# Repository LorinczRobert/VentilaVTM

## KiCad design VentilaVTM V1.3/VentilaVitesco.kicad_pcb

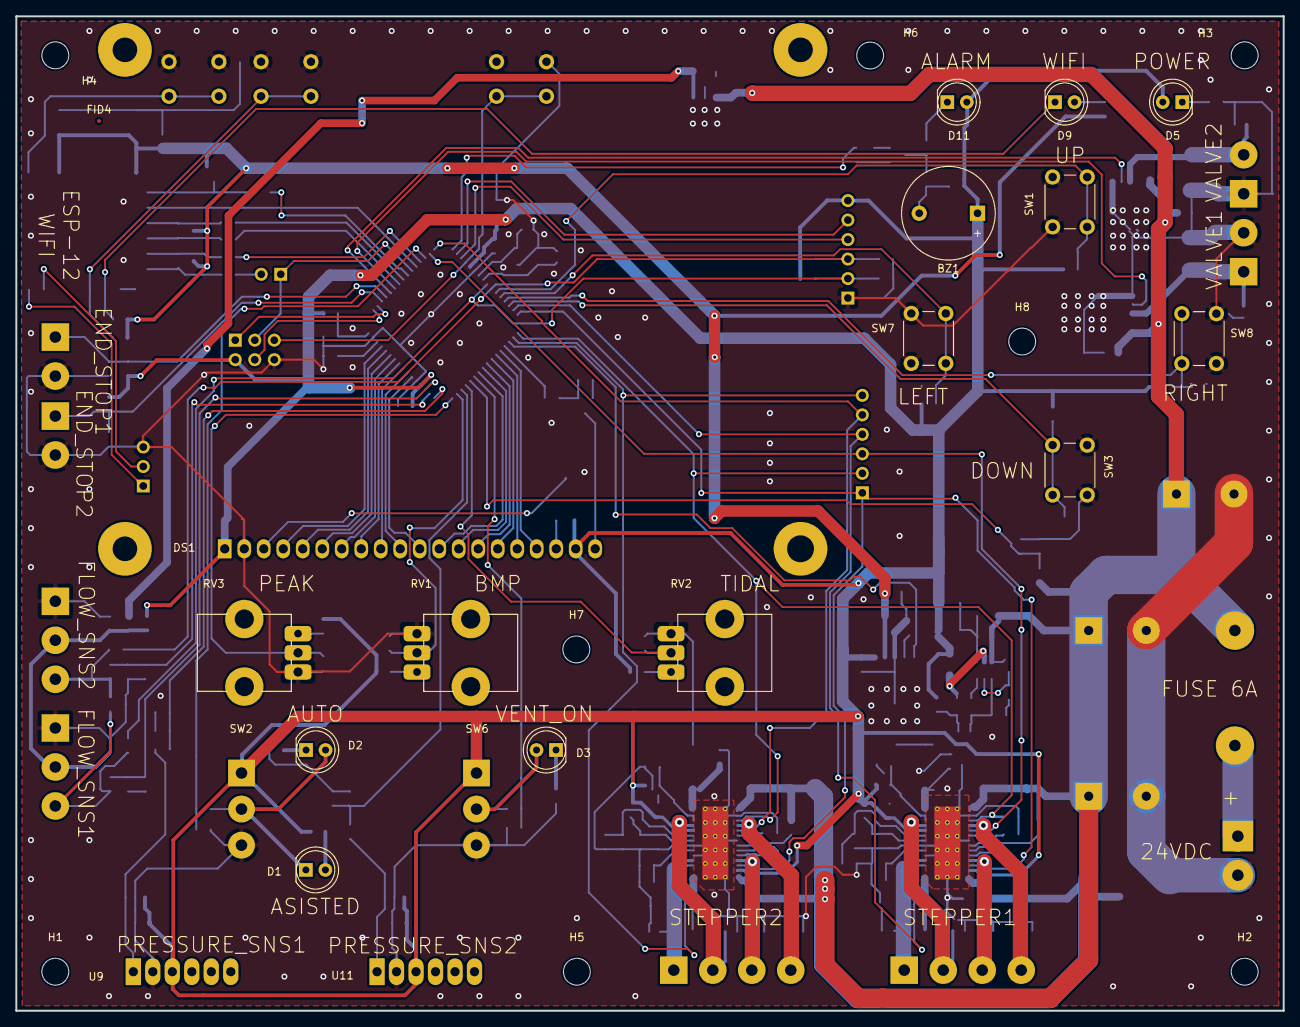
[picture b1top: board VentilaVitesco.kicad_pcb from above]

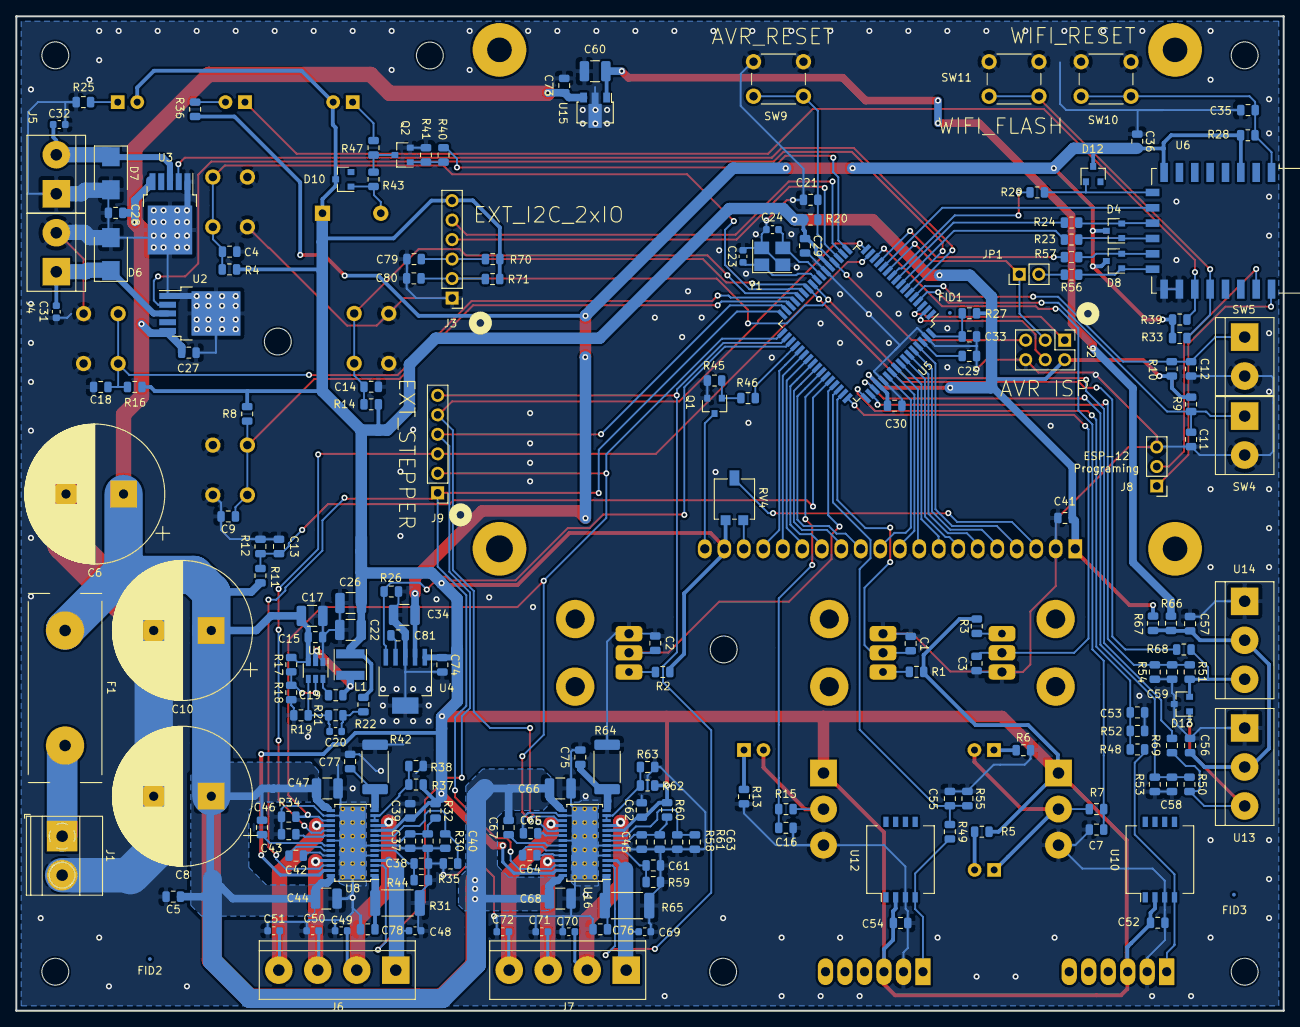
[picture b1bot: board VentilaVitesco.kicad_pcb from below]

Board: 2 copper layers, 165.1 x 129.5 mm, 224 parts (196 on the bottom side), 134 nets.

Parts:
BZ1: Buzzer; Buzzer_12x9.5RM7.6
C1, C2, C3, C4, C5, C7, C9, C11, C12, C13, C14, C15, C16, C18, C19, C21, C27, C28, C29, C30, C35, C37, C39, C41, C45, C52, C54, C56, C57, C58, C59, C62, C75, C76, C77, C78, C81: 100n; C_0805_2012Metric
C6, C8, C10: 4700u; CP_Radial_D18.0mm_P7.50mm_modificat
C17, C34, C44, C47, C60, C66, C68: 10u; C_1210_3225Metric
C20: 75p; C_0603_1608Metric
C22, C26: 22u; C_1210_3225Metric
C23: 10P; C_0603_1608Metric
C24: 10p; C_0603_1608Metric
C25: 220; C_0805_2012Metric
C31, C32, C48, C49, C50, C51, C69, C70, C71, C72: 10n; C_0603_1608Metric
C33, C36, C73, C74: 1u; C_0805_2012Metric
C38, C40, C61, C63: 1n; C_0805_2012Metric
C42, C43, C46, C53, C55, C64, C65, C67: 220n; C_0805_2012Metric
C79, C80: 100p; C_0805_2012Metric
D1, D2, D3, D5, D9, D11: LD271; LED_D5.0mm_IRGrey
D4, D8, D10, D12: BAV70; SOT-23
D6, D7: VSSB420s; D_SMB
D13: NUP2105L; SOT-23
DS1: AG12864E; AG12864E_big
F1: 6A; Fuseholder
FID1, FID2, FID3, FID4: Fiducial; Fiducial_0.5mm_Mask1mm
H1, H2, H3, H4, H5, H6, H7, H8: M3.5; MountingHole_3.5mm
J1: Screw_Terminal_01x02; TerminalBlock_Phoenix_MKDS-1,5-2-5.08_1x02_P5.08mm_Horizont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
J2: Conn_02x03_Odd_Even; PinHeader_2x03_P2.54mm_Vertical
J3, J9: Conn_01x06; PinHeader_1x06_P2.54mm_Vertical
J4, J5: Screw_Terminal_01x02; TerminalBlock_bornier-2_P5.08mm_BIGPADS
J6, J7: Screw_Terminal_01x04; TerminalBlock_bornier-4_P5.08mm_BIGPADS
J8: Conn_01x03; PinHeader_1x03_P2.54mm_Vertical
JP1: Jumper; PinHeader_1x02_P2.54mm_Vertical
L1: 15uH; L_Taiyo-Yuden_MD-4040
Q1, Q2: BC817; SOT-23
R1, R2, R3, R4, R7, R8, R9, R10, R12, R14, R15, R16, R18, R20, R23, R24, R26, R28, R33, R34, R39, R40, R46, R50, R51, R70, R71: 10k; R_0805_2012Metric
R5, R6, R13, R25, R29, R48, R49, R56, R57: 1k; R_0805_2012Metric
R11, R17, R21: 100k; R_0805_2012Metric
R19: 13.3k; R_0805_2012Metric
R22: 47; R_0805_2012Metric
R27: 10; R_0805_2012Metric
R30, R41, R45, R58: 22k; R_0805_2012Metric
R31, R35, R59, R61: 47k; R_0805_2012Metric
R32, R60: 33k; R_0805_2012Metric
R36, R47: 220; R_0805_2012Metric
R37, R62, R66, R68, R69: 0; R_0805_2012Metric
R38, R52, R53, R54, R55, R63, R67: NM; R_0805_2012Metric
R42, R44, R64, R65: 0.1; R_2512_6332Metric
R43: 75; R_0805_2012Metric
RV1, RV2, RV3: 10K; Potentiometer_Alps_RK09K_Single_Vertical_bolded
RV4: 10K; Potentiometer_Vishay_TS53YL_Vertical
SW1, SW3, SW7, SW8: SW_Push; SW_PUSH_6mm_H13mm
SW2, SW6: SW_SPDT; Toggleswicth
SW4, SW5: SW_DIP_x01; TerminalBlock_bornier-2_P5.08mm_BIGPADS
SW9, SW10, SW11: SW_Push; SW_PUSH_6mm_H5mm
U1: TPS54202DDCR; SOT-23-6
U2, U3: BTF50060; TO-252-5_TabPin6
U4: TPS73233DCQR; SOT-223-6
U5: ATmega64-16AU; TQFP-64_14x14mm_P0.8mm
U6: ESP-12E
U8, U16: DRV8818; HTSSOP-28-1EP_4.4x9.7mm_P0.65mm_EP3.4x9.5mm_ThermalVias
U9, U11: MPX5010DP; Pressure_SIP_V2
U10, U12: MPX5010_style2; Freescale_98ARH99089A
U13, U14: AWM720P1; TerminalBlock_bornier-3_P5.08mm_BIGPADS
U15: UA78L12ACPK; SOT-89-3
Y1: 16HMz; Oscillator_SMD_Abracon_ASE-4Pin_3.2x2.5mm_HandSoldering

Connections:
+3V3: C34.1, C36.2, D4.3, D8.3, D12.3, R28.1, R33.2, R36.1, R39.2, U4.2, U6.3, U6.8
+5V: BZ1.1, C22.1, C26.1, C29.1, C30.1, C39.1, C41.1, C52.1, C54.1, C62.1, C74.1, D5.2, D10.3, D11.2, DS1.1, DS1.19, J2.2, J3.6, L1.2, R1.2, R2.2, R3.2, R4.2, R5.2, R8.2, R9.2, R10.2, R14.2, R16.2, R20.2, R22.2, R27.2, R32.1, R37.2, R60.1, R62.2, R67.1, R70.2, R71.2, RV4.3, SW2.1, SW6.1, U4.1, U5.21, U5.52, U8.10, U8.27, U9.3, U10.2, U11.3, U12.2, U16.10, U16.27
+12V: C60.1, R66.1, U15.1
+24V: C5.1, C6.1, C8.1, C10.1, C15.1, C17.1, C27.1, C28.1, C44.2, C46.1, C47.2, C66.2, C67.1, C68.2, C73.1, F1.1, R11.2, R17.2, U1.3, U2.5, U3.5, U8.15, U8.28, U15.3, U16.15, U16.28
/A1: C48.1, J6.1, U8.4
/A2: C50.1, J6.3, U8.25
/A12: C69.1, J7.1, U16.4
/A22: C71.1, J7.3, U16.25
/B1: C49.1, J6.2, U8.11
/B2: C51.1, J6.4, U8.18
/B12: C70.1, J7.2, U16.11
/B22: C72.1, J7.4, U16.18
BACKLIGHT: R46.1, U5.36
BPM_ADC: C1.1, RV1.2, U5.47
BUZZER: R40.2, U5.17
END_STOP1: C12.1, R10.1, SW5.1, U5.5
END_STOP2: C11.1, R9.1, SW4.1, U5.4
EN_3V3: R26.2, U4.5, U5.35
FLOW_S1_ADC: C58.1, R50.1, R53.2, U5.51
FLOW_S2_ADC: C59.1, R51.1, R54.2, U5.50
GND: C1.2, C2.2, C3.2, C4.2, C5.2, C6.2, C7.2, C8.2, C9.2, C10.2, C11.2, C12.2, C13.2, C14.2, C15.2, C16.2, C17.2, C18.2, C21.2, C22.2, C23.2, C24.2, C25.2, C26.2, C27.2, C28.2, C29.2, C30.2, C31.2, C32.2, C33.1, C34.2, C35.2, C36.1, C37.2, C38.2, C39.2, C40.2, C41.2, C43.1, C44.1, C45.2, C47.1, C48.2, C49.2, C50.2, C51.2, C52.2, C53.1, C54.2, C55.1, C56.2, C57.2, C58.2, C59.2, C60.2, C61.2, C62.2, C63.2, C65.1, C66.1, C68.1, C69.2, C70.2, C71.2, C72.2, C73.2, C74.2, C75.2, C76.2, C77.2, C78.2, C79.2, C80.2, C81.2, D6.2, D7.2, D13.3, DS1.2, J1.2, J2.6, J3.1, J4.2, J5.1, J8.3, Q1.2, Q2.2, R6.2, R12.1, R13.2, R18.1, R19.2, R25.1, R26.1, R30.2, R31.1, R34.1, R35.1, R38.2, R41.1, R42.2, R44.2, R45.1, R52.1, R53.1, R54.1, R55.1, R58.2, R59.1, R61.1, R63.2, R64.2, R65.2, RV1.3, RV2.3, RV3.3, SW1.1, SW2.3, SW3.1, SW4.2, SW5.2, SW6.3, SW7.1, SW8.1, SW9.2, SW10.2, SW11.1, U1.1, U2.1, U2.6, U3.1, U3.6, U4.3, U4.6, U5.22, U5.53, U5.63, U6.15, U6.16, U8.5, U8.7, U8.16, U8.21, U8.29, U9.2, U10.3, U11.2, U12.3, U13.1, U14.1, U15.2, U16.5, U16.7, U16.16, U16.21, U16.29, Y1.2, Y1.4
I2C_SCL: C80.1, J3.2, R69.1, R71.1, U5.25
I2C_SDA: C79.1, J3.3, R68.1, R70.1, U5.26
ISP: J2.3, JP1.1, U5.11
LCD_D: DS1.16, U5.38
LCD_DB0: DS1.4, U5.61
LCD_DB1: DS1.5, U5.60
LCD_DB2: DS1.6, U5.59
LCD_DB3: DS1.7, U5.58
LCD_DB4: DS1.8, U5.57
LCD_DB5: DS1.9, U5.56
LCD_DB6: DS1.10, U5.55
LCD_DB7: DS1.11, U5.54
LCD_E: DS1.17, U5.37
LCD_RS: DS1.14, U5.40
LCD_RW: DS1.15, U5.39
LCD_nCS1: DS1.12, U5.42
LCD_nCS2: DS1.13, U5.41
MENU_DOWN: C9.1, R8.1, SW3.2, U5.30
MENU_LEFT: C14.1, R14.1, SW7.2, U5.28
MENU_RIGHT: C18.1, R16.1, SW8.2, U5.29
MENU_UP: C4.1, R4.1, SW1.2, U5.27
unnamed: BZ1.2, D10.1, R43.1
unnamed: C19.1, L1.1, U1.2
unnamed: C19.2, U1.6
unnamed: C20.1, R21.1, R22.1
unnamed: C20.2, R19.1, R21.2, U1.4
unnamed: C21.1, J2.5, R20.1, SW9.1, U5.20
unnamed: C23.1, U5.24, Y1.1
unnamed: C24.1, U5.23, Y1.3
unnamed: C25.1, U5.62
unnamed: C31.1, D6.1, J4.1, U2.3
unnamed: C32.1, D7.1, J5.2, U3.3
unnamed: C33.2, R27.1, U5.64
unnamed: C35.1, R28.2, SW10.1, U6.1
unnamed: C37.1, R30.1, R32.2, U8.8
unnamed: C38.1, R31.2, U8.6
unnamed: C40.1, R35.2, U8.9
unnamed: C42.1, U8.24
unnamed: C42.2, U8.23
unnamed: C43.2, U8.20
unnamed: C45.1, R58.1, R60.2, U16.8
unnamed: C46.2, U8.22
unnamed: C56.1, C57.1, R66.2, R67.2, U13.2, U14.2
unnamed: C61.1, R59.2, U16.6
unnamed: C63.1, R61.2, U16.9
unnamed: C64.1, U16.24
unnamed: C64.2, U16.23
unnamed: C65.2, U16.20
unnamed: C67.2, U16.22
unnamed: C75.1, R64.1, U16.14
unnamed: C76.1, R65.1, U16.1
unnamed: C77.1, R42.1, U8.14
unnamed: C78.1, R44.1, U8.1
unnamed: C81.1, U4.4
unnamed: D1.1, D2.2, R7.2, SW2.2
unnamed: D1.2, R5.1
unnamed: D2.1, R6.1
unnamed: D3.1, R13.1
unnamed: D3.2, R15.2, SW6.2
unnamed: D5.1, R25.2
unnamed: D9.1, R39.1, U6.17
unnamed: D9.2, R36.2
unnamed: D11.1, R47.1
unnamed: D13.1, R50.2, R69.2, U13.3
unnamed: D13.2, R51.2, R68.2, U14.3
unnamed: DS1.3, RV4.2
unnamed: DS1.18, RV4.1
unnamed: DS1.20, Q1.3
unnamed: F1.2, J1.1
unnamed: J2.1, U5.3
unnamed: J2.4, U5.2
unnamed: J3.4, U5.19
unnamed: J3.5, U5.18
unnamed: J8.1, U6.22
unnamed: J8.2, U6.21
unnamed: JP1.2, R56.2
unnamed: Q1.1, R45.2, R46.2
unnamed: Q2.1, R40.1, R41.2
unnamed: Q2.3, R43.2, R47.2
unnamed: R1.1, RV1.1
unnamed: R2.1, RV2.1
unnamed: R3.1, RV3.1
unnamed: R17.1, R18.2, U1.5
unnamed: R23.1, U5.8
unnamed: R24.1, U5.9
unnamed: R29.2, U5.10
unnamed: R33.1, SW11.2, U6.18
unnamed: R37.1, R38.1, U8.12, U8.13
unnamed: R48.2, U9.1, U10.4
unnamed: R49.2, U11.1, U12.4
unnamed: R57.2, U5.13
unnamed: R62.1, R63.1, U16.12, U16.13
ON_OFF_VENT: C16.1, R15.1, U5.43
PEAK_ADC: C3.1, RV3.2, U5.48
PS1_ADC: C53.2, R48.1, R52.2, U5.49
PS2_ADC: C55.2, R49.1, R55.2, U5.46
STEP1: J9.3, U5.15, U8.19
STEP2: J9.5, U5.16, U16.19
STEPPER_nENABLE: J9.1, U5.32, U8.26, U16.26
STEP_DIR1: J9.4, U5.31, U8.3
STEP_DIR2: J9.6, U5.34, U16.3
TIDAL_ADC: C2.1, RV2.2, U5.45
V24_ADC: C13.1, R11.1, R12.2, U5.44
VALVE1: U2.2, U5.7
VALVE2: U3.2, U5.6
VENT_MODE: C7.1, R7.1, U5.14
WIFI_CS: D12.1, R29.1, U6.9
WIFI_IO1: D4.2, R24.2, U6.11
WIFI_IO2: D4.1, R23.2, U6.12
WIFI_MISO: U5.12, U6.10
WIFI_MOSI: D8.2, R57.1, U6.13
WIFI_SCK: D8.1, R56.1, U6.14
nRESET_STEPPER: J9.2, R34.2, U5.33, U8.17, U16.17
